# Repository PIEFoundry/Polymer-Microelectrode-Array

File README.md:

# Polymer Microelectrode Array
This repository contains all files relevant to the design and manufacture of the PIE Foundry polymer microelectrode arrays. For more information about the PIE Foundry, visit our [website](https://piefoundry.usc.edu/). <br>
Please cite this repository using the DOI below <br> 

## Organization
[Protocols](/Protocols) directory holds up-to-date protocols and subprotocols for PMEA microfabrication and PCB attachment/packaging. PDF files are updated with each release. <br>
[Designs](/Designs) directory holds lithographic designs of open-source PMEAs produced by the PIE Foundry, including component designs for lithographic masks, and PCB designs of common adapter boards. Lithographic designs are stored as .dxf and PCB designs are stored as gerber files and Eagle schematics. <Br>
[Resource](/Resources/) directory holds PIE Foundry generated Eagle libraries, including for common PMEA wirebond connector layouts and Omnetics brand analog connector solder pad layouts, as well as useful solid files. Solid files are stored in STEP format. 

## License
All files in this repository are released under the CC-BY 4.0 International copyright license

## Disclaimer
The contents of this repository are subject to revision. No representation or warranty, express or implied, is provided in relation to the accuracy, correctness, completeness, or reliability of the information, opinions, or conclusions expressed in this repository.

The contents of this repository (the “Materials”) are experimental in nature and should be used with prudence and appropriate caution. Any use is voluntary and at your own risk.

The Materials are made available “as is” by USC (the University of Southern California and its trustees, directors, officers, employees, faculty, students, agents, affiliated organizations and their insurance carriers, if any), and any other contributors to this repository (collectively, “Providers”). Providers expressly disclaim all warranties, express or implied, arising in connection with the Materials, or arising out of a course of performance, dealing, or trade usage, including, without limitation, any warranties of title, noninfringement, merchantability, or fitness for a particular purpose.

Any user of the Materials agrees to forever indemnify, defend, and hold harmless Providers from and against, and to waive any and all claims against Providers for any and all claims, suits, demands, liability, loss or damage whatsoever, including attorneys' fees, whether direct or consequential, on account of any loss, injury, death or damage to any person or (including without limitation all agents and employees of Providers and all property owned by, leased to or used by either Providers) or on account of any loss or damages to business or reputations or privacy of any persons, arising in whole or in part in any way from use of the Materials or in any way connected therewith or in any way related thereto.

The Materials, any related materials, and all intellectual property therein, are owned by Providers.

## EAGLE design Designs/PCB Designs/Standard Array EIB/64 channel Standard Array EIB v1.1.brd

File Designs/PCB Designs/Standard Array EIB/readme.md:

PCB design file set for 64 channel Standard Array EIB

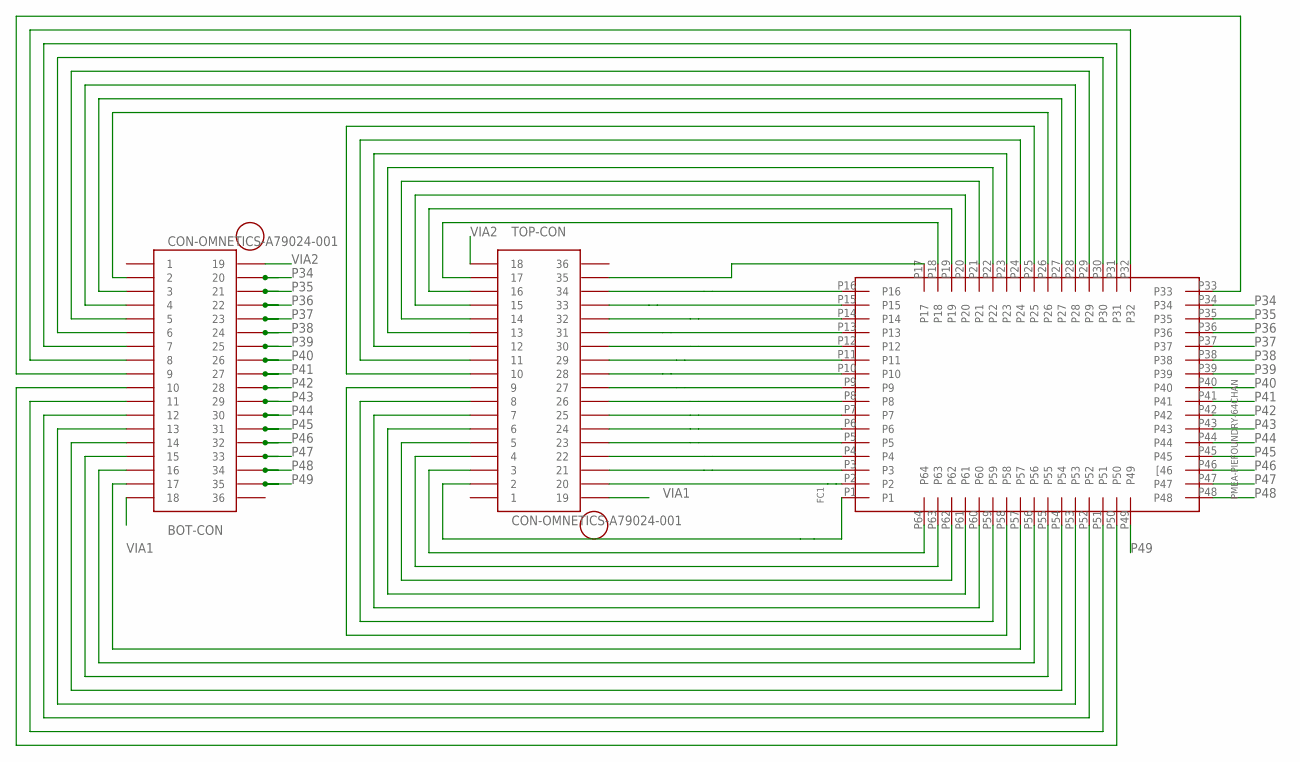
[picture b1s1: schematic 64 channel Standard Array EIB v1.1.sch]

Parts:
BOT-CON: CON-OMNETICS-A79024-001
FC1: PMEA-PIEFOUNDRY-64CHAN
TOP-CON: CON-OMNETICS-A79024-001

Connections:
unnamed: FC1.P17, TOP-CON.35
unnamed: FC1.P16, TOP-CON.34
unnamed: FC1.P15, TOP-CON.33
unnamed: FC1.P14, TOP-CON.32
unnamed: FC1.P13, TOP-CON.31
unnamed: FC1.P12, TOP-CON.30
unnamed: FC1.P11, TOP-CON.29
unnamed: FC1.P10, TOP-CON.28
unnamed: FC1.P9, TOP-CON.27
unnamed: FC1.P8, TOP-CON.26
unnamed: FC1.P7, TOP-CON.25
unnamed: FC1.P6, TOP-CON.24
unnamed: FC1.P5, TOP-CON.23
unnamed: FC1.P4, TOP-CON.22
unnamed: FC1.P3, TOP-CON.21
unnamed: FC1.P2, TOP-CON.20
unnamed: FC1.P18, TOP-CON.17
unnamed: FC1.P19, TOP-CON.16
unnamed: FC1.P20, TOP-CON.15
unnamed: FC1.P21, TOP-CON.14
unnamed: FC1.P22, TOP-CON.13
unnamed: FC1.P23, TOP-CON.12
unnamed: FC1.P24, TOP-CON.11
unnamed: FC1.P25, TOP-CON.10
unnamed: FC1.P1, TOP-CON.2
unnamed: FC1.P64, TOP-CON.3
unnamed: FC1.P63, TOP-CON.4
unnamed: FC1.P62, TOP-CON.5
unnamed: FC1.P61, TOP-CON.6
unnamed: FC1.P60, TOP-CON.7
unnamed: FC1.P59, TOP-CON.8
unnamed: FC1.P58, TOP-CON.9
unnamed: BOT-CON.2, FC1.P26
unnamed: BOT-CON.3, FC1.P27
unnamed: BOT-CON.4, FC1.P28
unnamed: BOT-CON.5, FC1.P29
unnamed: BOT-CON.6, FC1.P30
unnamed: BOT-CON.7, FC1.P31
unnamed: BOT-CON.8, FC1.P32
unnamed: BOT-CON.9, FC1.P33
unnamed: BOT-CON.17, FC1.P57
unnamed: BOT-CON.16, FC1.P56
unnamed: BOT-CON.15, FC1.P55
unnamed: BOT-CON.14, FC1.P54
unnamed: BOT-CON.13, FC1.P53
unnamed: BOT-CON.12, FC1.P52
unnamed: BOT-CON.11, FC1.P51
unnamed: BOT-CON.10, FC1.P50
P34: BOT-CON.20, FC1.P34
P35: BOT-CON.21, FC1.P35
P36: BOT-CON.22, FC1.P36
P37: BOT-CON.23, FC1.P37
P38: BOT-CON.24, FC1.P38
P39: BOT-CON.25, FC1.P39
P40: BOT-CON.26, FC1.P40
P41: BOT-CON.27, FC1.P41
P42: BOT-CON.28, FC1.P42
P43: BOT-CON.29, FC1.P43
P44: BOT-CON.30, FC1.P44
P45: BOT-CON.31, FC1.P45
P46: BOT-CON.32, FC1.P46 ([46)
P47: BOT-CON.33, FC1.P47
P48: BOT-CON.34, FC1.P48
P49: BOT-CON.35, FC1.P49
VIA1: BOT-CON.18, TOP-CON.19
VIA2: BOT-CON.19, TOP-CON.18

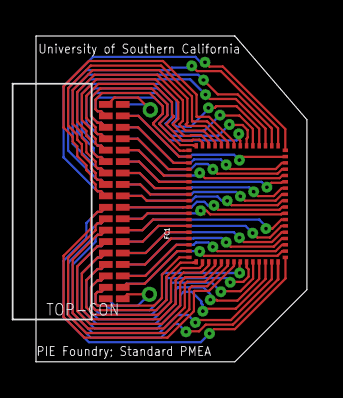
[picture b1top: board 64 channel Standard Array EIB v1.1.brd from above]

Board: 2 copper layers, 15.1 x 18.1 mm, 3 parts (1 on the bottom side), 66 nets.

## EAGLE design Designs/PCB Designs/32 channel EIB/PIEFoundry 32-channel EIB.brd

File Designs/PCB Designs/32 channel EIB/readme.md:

PCB design file set for 32 channel EIB

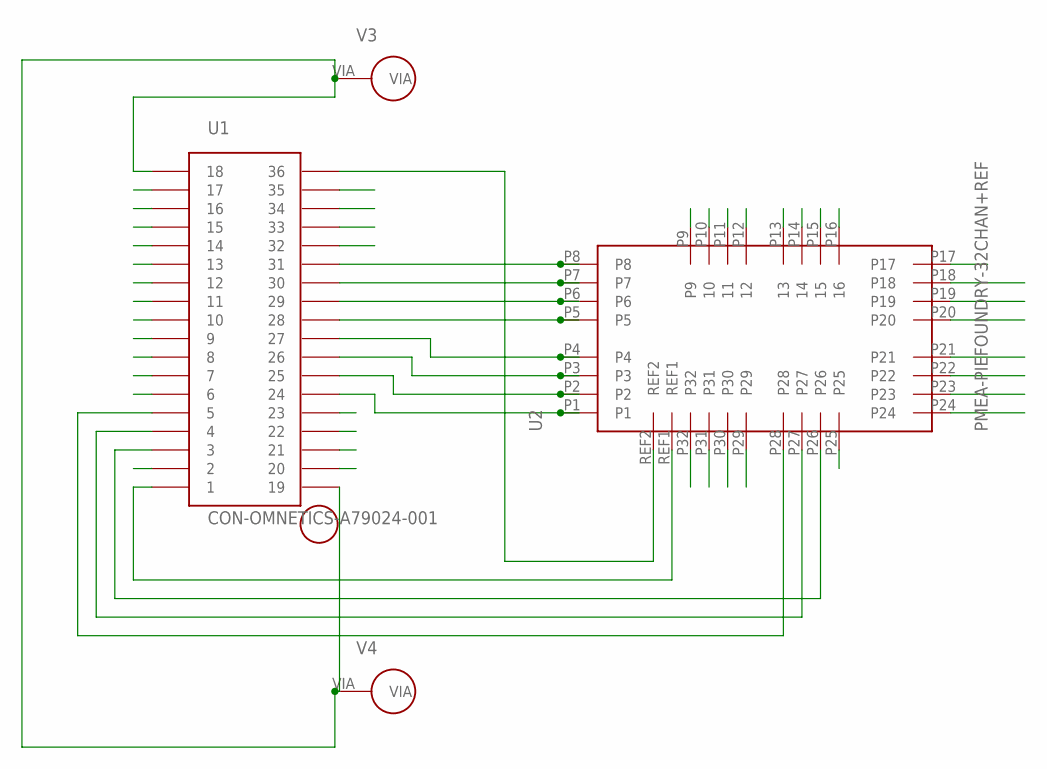
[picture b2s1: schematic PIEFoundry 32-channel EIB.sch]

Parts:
U1: CON-OMNETICS-A79024-001
U2: PMEA-PIEFOUNDRY-32CHAN+REF
V3, V4: SOLDER_VIA_500_UM

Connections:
GND: U1.18, U1.19, V3.VIA, V4.VIA
P1: U1.24, U2.P1
P2: U1.25, U2.P2
P3: U1.26, U2.P3
P4: U1.27, U2.P4
P5: U1.28, U2.P5
P6: U1.29, U2.P6
P7: U1.30, U2.P7
P8: U1.31, U2.P8
P9: U1.20, U2.P9
P10: U1.21, U2.P10 (10)
P11: U1.22, U2.P11 (11)
P12: U1.23, U2.P12 (12)
P13: U1.32, U2.P13 (13)
P14: U1.33, U2.P14 (14)
P15: U1.34, U2.P15 (15)
P16: U1.35, U2.P16 (16)
P17: U1.6, U2.P17
P18: U1.7, U2.P18
P19: U1.8, U2.P19
P20: U1.9, U2.P20
P21: U1.10, U2.P21
P22: U1.11, U2.P22
P23: U1.12, U2.P23
P24: U1.13, U2.P24
P25: U1.2, U2.P25
P26: U1.3, U2.P26
P27: U1.4, U2.P27
P28: U1.5, U2.P28
P29: U1.14, U2.P29
P30: U1.15, U2.P30
P31: U1.16, U2.P31
P32: U1.17, U2.P32
P33: U1.1, U2.REF1
P34: U1.36, U2.REF2

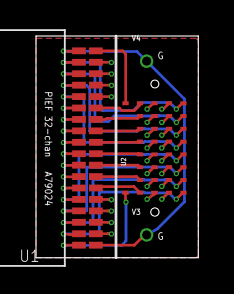
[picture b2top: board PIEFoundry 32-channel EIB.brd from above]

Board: 4 copper layers, 9.0 x 12.3 mm, 4 parts (0 on the bottom side), 35 nets.

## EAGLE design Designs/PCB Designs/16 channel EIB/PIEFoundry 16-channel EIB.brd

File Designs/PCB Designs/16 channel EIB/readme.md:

PCB design file set for 16 channel EIB

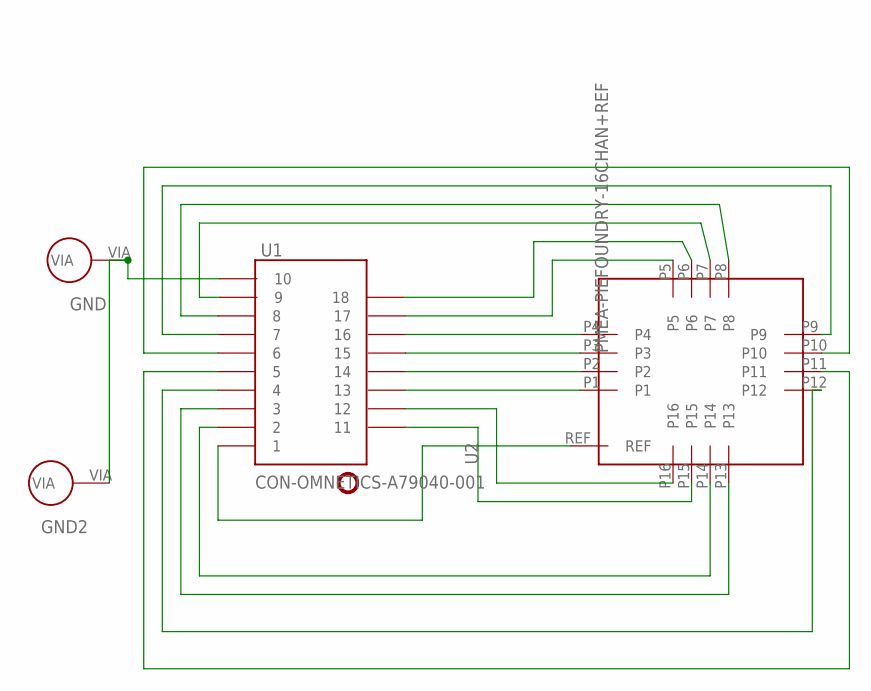
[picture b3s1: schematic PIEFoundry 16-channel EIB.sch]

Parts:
GND, GND2: SOLDER_VIA_500_UM
U1: CON-OMNETICS-A79040-001
U2: PMEA-PIEFOUNDRY-16CHAN+REF

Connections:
GND: GND.VIA, GND2.VIA, U1.10
unnamed: U1.13, U2.P1
unnamed: U1.14, U2.P2
unnamed: U1.15, U2.P3
unnamed: U1.16, U2.P4
unnamed: U1.12, U2.P16
unnamed: U1.11, U2.P15
unnamed: U1.17, U2.P5
unnamed: U1.18, U2.P6
unnamed: U1.2, U2.P14
unnamed: U1.3, U2.P13
unnamed: U1.8, U2.P8
unnamed: U1.9, U2.P7
unnamed: U1.4, U2.P12
unnamed: U1.5, U2.P11
unnamed: U1.6, U2.P10
unnamed: U1.7, U2.P9
unnamed: U1.1, U2.REF

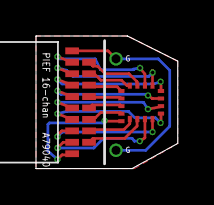
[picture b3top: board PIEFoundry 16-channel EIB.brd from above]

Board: 2 copper layers, 7.9 x 7.4 mm, 4 parts (0 on the bottom side), 18 nets.

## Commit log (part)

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2024-12-18 Created design folder and readme
2024-12-18 Added protocols
2024-12-18 created subprotocol directory
2024-12-30 Added corrected MPW protocol
    Typo in 3.2
2024-12-30 Corrected MPW protocol
    typo in 3.2
2024-12-30 Most recent PIE Foundry standard array CADdesigns
2024-12-30 Rename Designs/Standard Array v1.3 15micron - MaskSet.dxf to Designs/Lithographic Designs/Standard Array v1.3 15micron - MaskSet.dxf
    Folder move
2024-12-30 Rename Designs/Standard Array v1.3 15micron.dxf to Designs/Lithographic Designs/Standard Array v1.3 15micron.dxf
    Folder move
2024-12-30 Rename Designs/Standard Array v1.61 30 micron - MaskSet.dxf to Designs/Lithographic Designs/Standard Array v1.61 30 micron - MaskSet.dxf
    Folder move
2024-12-30 Rename Designs/Standard Array v1.61 30 micron.dxf to Designs/Lithographic Designs/Standard Array v1.61 30 micron.dxf
    Folder move
2024-12-30 Create PCB designs folder
2025-01-03 Standard Array folder
2025-01-03 Update and rename Designs/Lithographic Designs/Standard Array v1.3 15micron - MaskSet.dxf to Designs/Lithographic Designs/Standard Array/Standard Array v1.3 15micron - MaskSet.dxf
    Folder move
2025-01-03 Update and rename Designs/Lithographic Designs/Standard Array v1.3 15micron.dxf to Designs/Lithographic Designs/Standard Array/Standard Array v1.3 15micron.dxf
    Folder move
2025-01-03 Update and rename Designs/Lithographic Designs/Standard Array v1.61 30 micron - MaskSet.dxf to Designs/Lithographic Designs/Standard Array/Standard Array v1.61 30 micron - MaskSet.dxf
    Folder move
2025-01-03 Update and rename Designs/Lithographic Designs/Standard Array v1.61 30 micron.dxf to Designs/Lithographic Designs/Standard Array/Standard Array v1.61 30 micron.dxf
    Folder move
2025-01-03 Rename Tetrode v1 15micron.dxf to Tetrode v1 15micron.dxf
    Folder move
2025-01-03 Tetrode v1 designs
    30 and 15 micron tetrode v1 designs
2025-01-04 Test Structure designs
2025-01-04 Update and rename Designs/Lithographic Designs/Test Structure v1.dxf to Designs/Lithographic Designs/Miscellaneous/Test Structure v1.dxf
    folder move
2025-01-04 Update and rename Designs/Lithographic Designs/Test Structure v1 - MaskSet.dxf to Designs/Lithographic Designs/Miscellaneous/Test Structure v1 - MaskSet.dxf
    Folder move
2025-03-20 Added most recent masktemplate/alignment mark files
2025-03-21 Creates images directory
2025-03-21 simplified file name
2025-03-21 Update PMEA Microfabrication.md
    Fixed image display, minor syntax issues
2025-03-21 Update SubProtocol_Etch Mask Lithography.md
    minor syntax changes
2025-03-21 Update SubProtocol_Metal Patterning via Lift-Off.md
    minor syntax changes
2025-03-21 Moved to PDF folder
2025-03-21 moved to PDFs folder
2025-03-21 Rename Protocols/PMEA PCB Attachment.pdf to Protocols/PDFs/PMEA PCB Attachment.pdf
2025-03-26 Added con-omnetics library
2025-03-26 Rename Resources/con-omnetics.lbr to Resources/Libraries/con-omnetics.lbr
2025-03-26 Added pmea-piefoundry library
2025-03-26 Added 16-channel EIB board file
2025-03-26 Created 16 channel EIB folder
2025-03-26 Added 16-channel EIB PCB design file set
2025-03-26 32-channel EIB fileset added
2025-03-26 Rename Designs/PCB Designs/PIEFoundry 32-channel EIB.brd to Designs/PCB Designs/32 channel EIB/PIEFoundry 32-channel EIB.brd
2025-03-26 moved file
2025-03-26 corrected folder name
2025-03-26 Added standard array board file
2025-03-26 Updated full standard array eib fileset
2025-03-26 Added 16-channel EIB drawing
2025-03-26 Fixed link
2025-03-26 Images for PCB design folder readme.md
2025-03-26 16channel readme
2025-03-26 Rename 16 channel EIB.png to 16 channel_EIB.png
2025-03-26 Rename 16 channel_EIB.png to 16_channel_EIB.png
2025-03-26 Fixed link typo
2025-03-26 Rename 32 channel EIB.png to 32_channel_EIB.png
2025-03-26 Rename 64 channel Standard Array EIB.png to 64_channel_Standard_Array-EIB.png
2025-03-26 Rename Resources/A79016-001.ipt to Resources/Solids/A79016-001.ipt
2025-04-02 Update README.md with license info
2025-04-08 Corrected broken link
2025-04-08 Added DOI to readme
2025-04-18 Update CITATION.cff
    Corrected wrong author name
2026-01-30 Revise PMEA Microfabrication protocol parameters v1.03
    Updated various parameters and processes in the PMEA Microfabrication protocol, including photoresist thickness targets, annealing temperatures, and cleaning recipes.
2026-01-30 Revise lithography parameters for better results v1.03
    Updated spin acceleration, exposure dose, and baking times for improved lithography process.
2026-01-30 Revise soak time and ultrasonic bath duration v1.03
    Updated soak duration and ultrasonic bath application time for improved clarity.
